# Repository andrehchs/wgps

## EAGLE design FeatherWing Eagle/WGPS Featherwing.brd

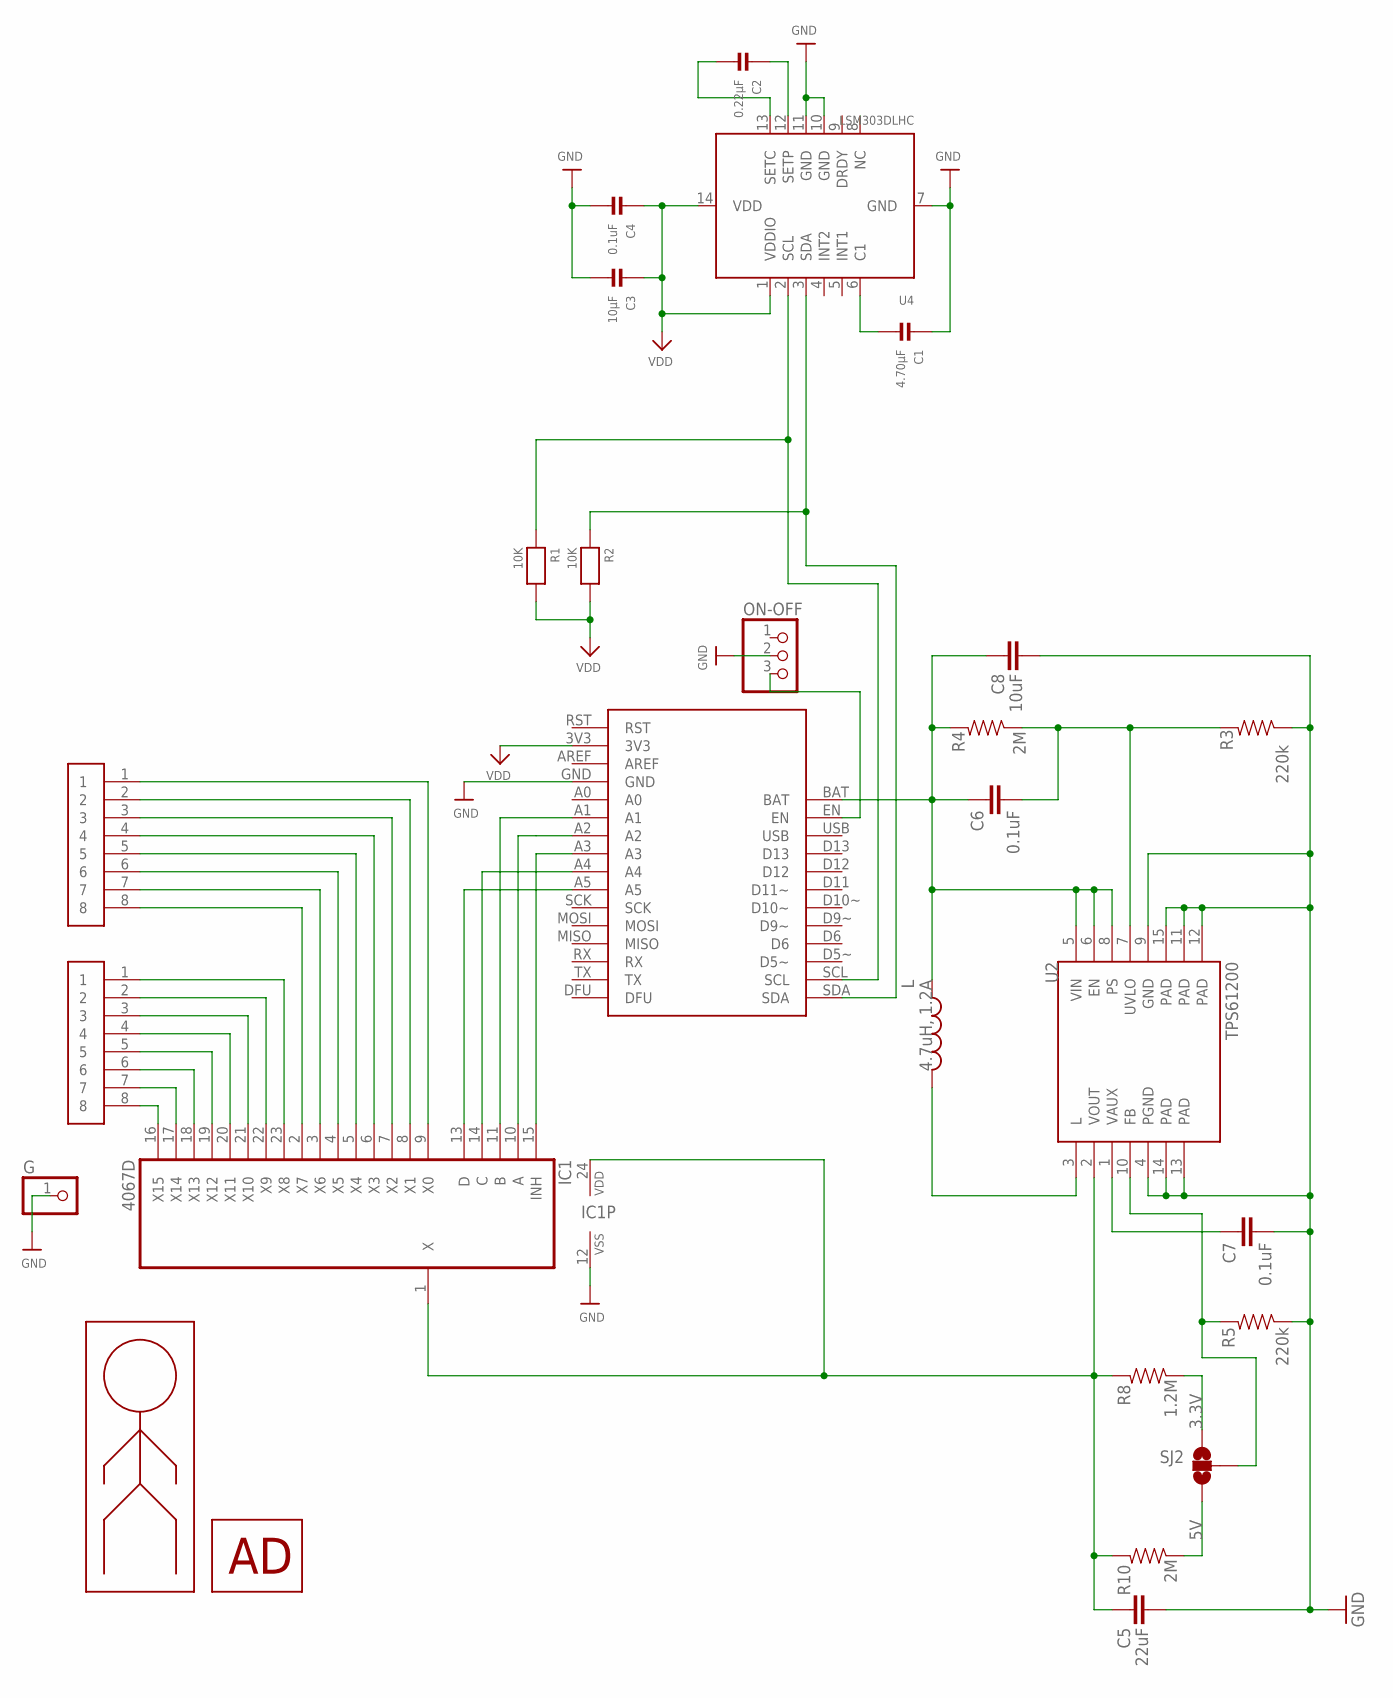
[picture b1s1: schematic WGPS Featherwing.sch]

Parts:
C1: 4.70µF; _0805
C2: 0.22µF; _0805
C3: 10µF; _0805
C4: 0.1uF; _0805
C5: 22uF; 0805
C6, C7: 0.1uF; 0603-CAP
C8: 10uF; 1206
G: PINHD-1X1CB; 1X01-CLEANBIG
IC1: 4067D; SO24W
L: 4.7uH, 1.2A; CDRH2D09
ON-OFF: UXCELL_SWITCHCB; 1X03-CLEANBIG
R1, R2: 10K; _0805
R3, R5: 220k; 0603-RES
R4, R10: 2M; 0603-RES
R8: 1.2M; 0603-RES
SJ2: SOLDERJUMPER_2WAYPASTE2&3; SJ_3_PASTE2&3
U2: TPS61200; QFN-10_PAD
U4: LSM303DLHC; LGA14
U$1: SMD_FEATHERWING_BLE_32U4; FEATHERWING_MALE_SMD_HEADERS_0.1
U$3: AD_LOGO; AD_LOGO_0.25IN
U$6, U$7: SMD_JST_1X8
U$16: MAN_LOGO; MAN_LOGO_0.6

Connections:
3.3V: R8.1, SJ2.1
5V: R10.1, SJ2.3
5V+: C5.1, IC1.1 (X), IC1.24 (VDD), R8.2, R10.2, U2.2 (VOUT)
BAT: C6.1, C8.1, L.P$2 (2), R4.2, U2.5 (VIN), U2.6 (EN), U2.8 (PS), U$1.BAT
C1: C1.2, U4.6 (C1)
C2.A: C2.1, U4.12 (SETP)
C2.B: C2.2, U4.13 (SETC)
FB1: R5.2, SJ2.2, U2.10 (FB)
GND: C1.1, C3.2, C4.2, C5.2, C7.2, C8.2, G.1, IC1.12 (VSS), ON-OFF.2, R3.1, R5.1, U2.4 (PGND), U2.9 (GND), U2.11 (PAD), U2.12 (PAD), U2.13 (PAD), U2.14 (PAD), U2.15 (PAD), U4.7 (GND), U4.10 (GND), U4.11 (GND), U$1.GND
L: L.P$1 (1), U2.3 (L)
MUX.0: IC1.9 (X0), U$6.1
MUX.1: IC1.8 (X1), U$6.2
MUX.2: IC1.7 (X2), U$6.3
MUX.3: IC1.6 (X3), U$6.4
MUX.4: IC1.5 (X4), U$6.5
MUX.5: IC1.4 (X5), U$6.6
MUX.6: IC1.3 (X6), U$6.7
MUX.7: IC1.2 (X7), U$6.8
MUX.8: IC1.23 (X8), U$7.1
MUX.9: IC1.22 (X9), U$7.2
MUX.10: IC1.21 (X10), U$7.3
MUX.11: IC1.20 (X11), U$7.4
MUX.12: IC1.19 (X12), U$7.5
MUX.13: IC1.18 (X13), U$7.6
MUX.14: IC1.17 (X14), U$7.7
MUX.15: IC1.16 (X15), U$7.8
MUX.A: IC1.10 (A), U$1.A2
MUX.B: IC1.11 (B), U$1.A1
MUX.C: IC1.14 (C), U$1.A4
MUX.D: IC1.13 (D), U$1.A5
MUX.INH: IC1.15 (INH), U$1.A3
unnamed: ON-OFF.3, U$1.EN
unnamed: C7.1, U2.1 (VAUX)
SCL: R1.1, U4.2 (SCL), U$1.SCL
SDA: R2.1, U4.3 (SDA), U$1.SDA
UVLO1: C6.2, R3.2, R4.1, U2.7 (UVLO)
VDD: C3.1, C4.1, R1.2, R2.2, U4.1 (VDDIO), U4.14 (VDD), U$1.3V3

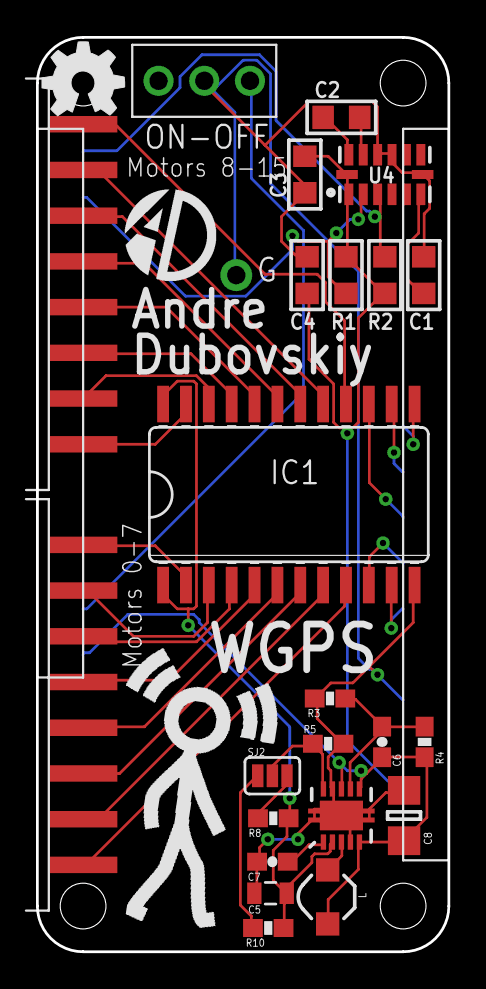
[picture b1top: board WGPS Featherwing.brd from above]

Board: 2 copper layers, 22.9 x 50.8 mm, 28 parts (0 on the bottom side), 37 nets.

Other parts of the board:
U$15: OSHW_5MM

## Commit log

2017-10-15 compiled files for Hackaday page

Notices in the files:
parts and their libraries:
microbuilder: This work is placed in the public domain, and may be freely used for commercial and non-commercial work with the following conditions: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
